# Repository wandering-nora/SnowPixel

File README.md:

# SnowPixel
Yet another 8x8 neopixel matrix... But hear me out, this one is a little special ❄️ 

This is a small 20x20x1.3mm module that can be seamlessly tiled without any wiring by soldering them together with the castellated holes.  
The built in solder jumpers in the data pads let the user decide whether the module sends and receives the data straight accross or at a 90 degree angle making any configuration possible.

The modules are meant to be used standalone or as an smd component in and of itself.  
The leds used are XL-1010RGBC-WS2812B 1x1mm leds which are the smallest currently available.  
If you have a clean 5V supply the capacitors on the back are usually not needed.  
This project is meant mainly as a test to push the pcb fab's specs to the limit and try a couple 3D printing ideas to obtain a thin, seamless display.

## 3D print
The 3D printed case is what brings the SnowPixel to life giving it proper square pixels. There's a standalone version for generic use and an smd version for when the pcb is soldered directly on a bigger pcb.  

The STL folder contains a bunch of common configurations, but the models are fully modular and can be easily edited with the OpenSCAD files.  

I'm currently experimenting with two methods for diffusing the light.  

### PET
These models are meant to be printed with PET (not PETG) on a PET diffusion film substrate.
This can be done by modifying a little the G-code to add an offset equal to the thickness of the film.

### PLA
These models are much simpler to print, they can be printed with normal pla (or any other plastic really) and only need the first layer to be printed in white and the rest in black.

 > Not an amazing render, I will update it with proper photos soon

## Manufacturing update
Even if quite out of spec for JLCPCB's cheapest offering (not paying for castellated holes and definitely going over spec for both the copper and silkscreen layers) the boards all turned out mostly fine!  
They definitely needed some cleanup as the edges were filled with burs from the castellated holes and the LED silkscreen wasn't printed all the way around.  
The boards are otherwise perfectly functional and pretty simple to assemble by hand with an hotplate.

#### Todo for v1.2
- [ ] Modify data jumpers for easier operation. (Maybe cuttable traces?)
- [ ] Make leds silkscreen thicker.

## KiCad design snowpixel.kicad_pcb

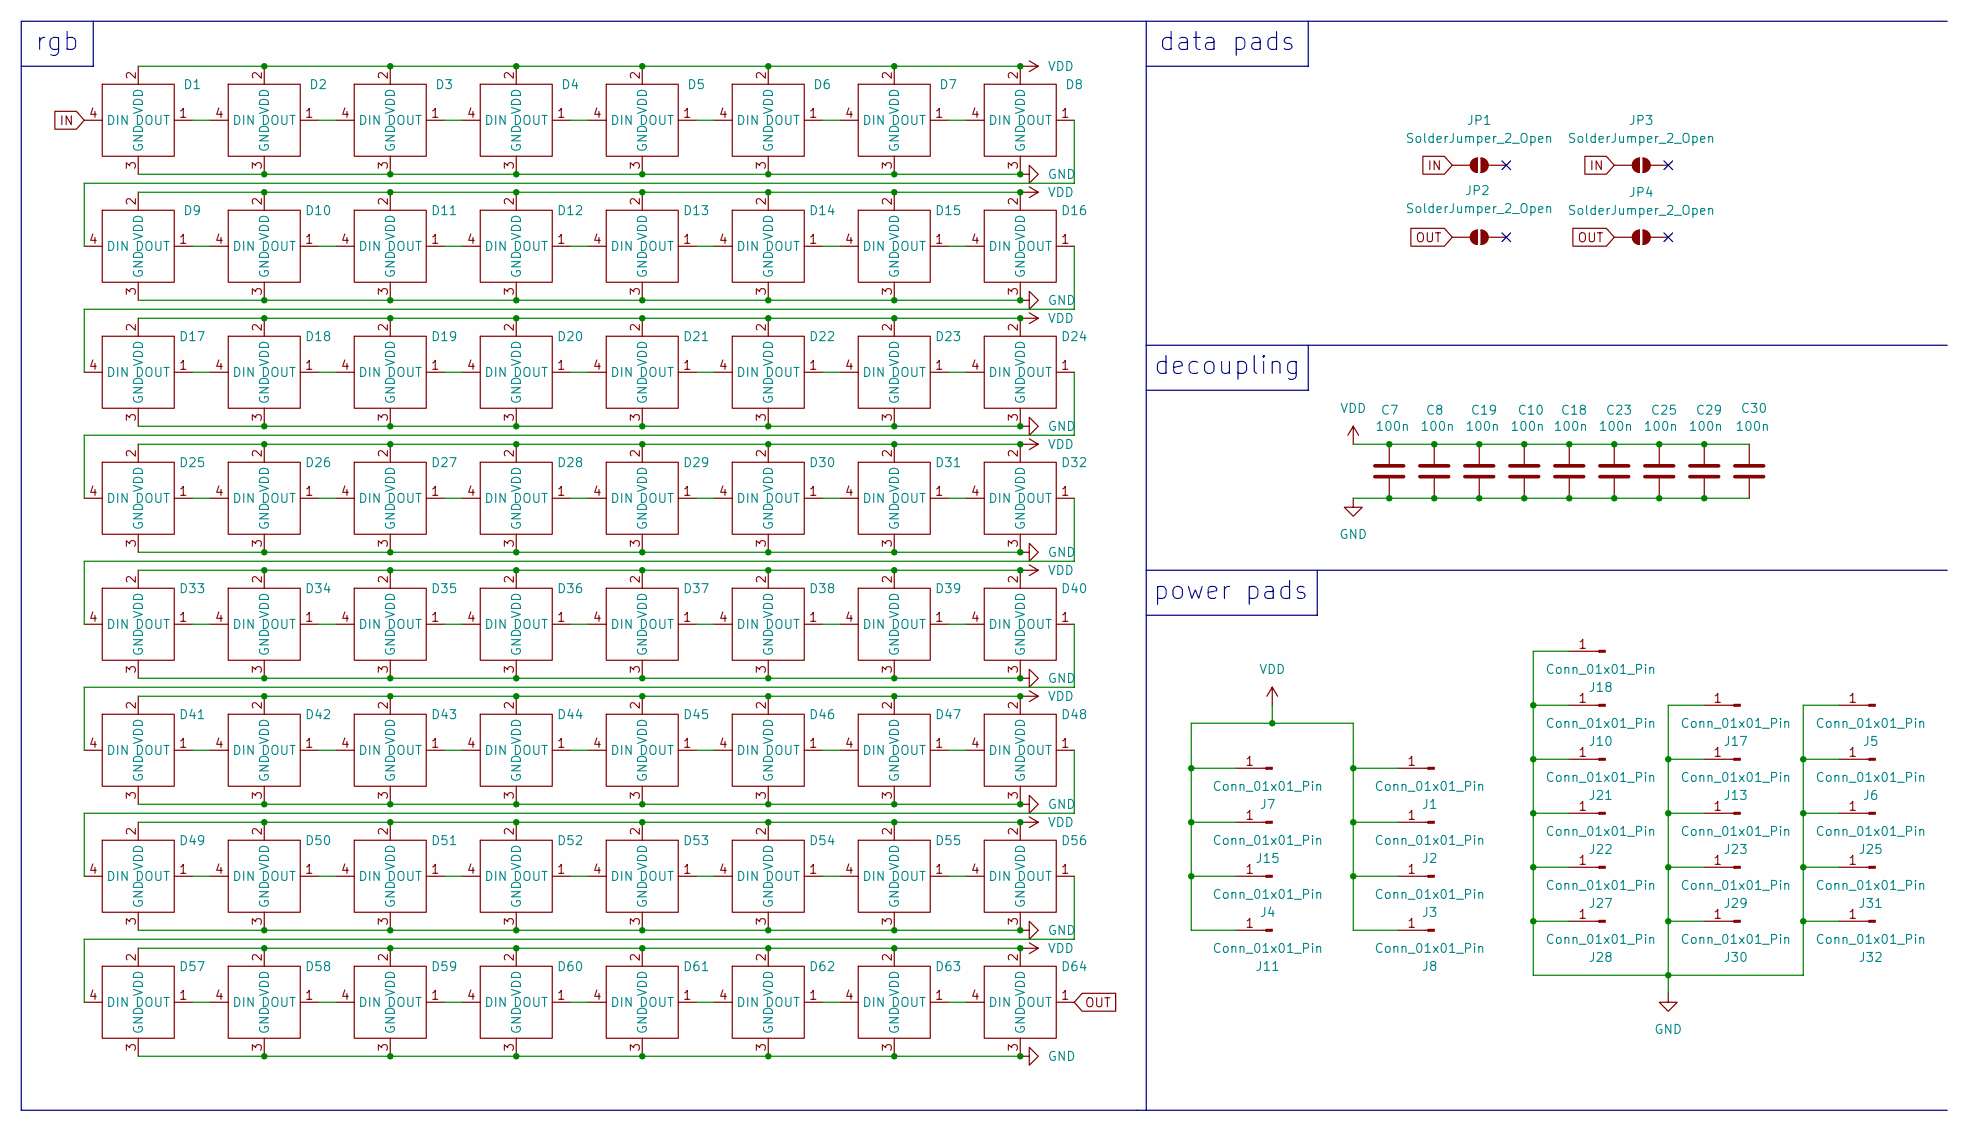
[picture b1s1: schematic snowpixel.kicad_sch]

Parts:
C7, C8, C10, C18, C19, C23, C25, C29, C30: 100n; C_0402_1005Metric
D1, D2, D3, D4, D5, D6, D7, D8, D9, D10, D11, D12, D13, D14, D15, D16, D17, D18, D19, D20, D21, D22, D23, D24, D25, D26, D27, D28, D29, D30, D31, D32, D33, D34, D35, D36, D37, D38, D39, D40, D41, D42, D43, D44, D45, D46, D47, D48, D49, D50, D51, D52, D53, D54, D55, D56, D57, D58, D59, D60, D61, D62, D63, D64: XL-1010RGBC-WS28128B
J1, J2, J3, J4, J7, J8, J11, J15: Conn_01x01_Pin; matrix-pad-vcc
J5, J6, J10, J13, J17, J18, J21, J22, J23, J25, J27, J28, J29, J30, J31, J32: Conn_01x01_Pin; matrix-pad-gn
JP1, JP3: SolderJumper_2_Open; matrix-pad-din
JP2, JP4: SolderJumper_2_Open; matrix-pad-dout

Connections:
GND: C7.2, C8.2, C10.2, C18.2, C19.2, C23.2, C25.2, C29.2, C30.2, D1.3 (GND), D2.3 (GND), D3.3 (GND), D4.3 (GND), D5.3 (GND), D6.3 (GND), D7.3 (GND), D8.3 (GND), D9.3 (GND), D10.3 (GND), D11.3 (GND), D12.3 (GND), D13.3 (GND), D14.3 (GND), D15.3 (GND), D16.3 (GND), D17.3 (GND), D18.3 (GND), D19.3 (GND), D20.3 (GND), D21.3 (GND), D22.3 (GND), D23.3 (GND), D24.3 (GND), D25.3 (GND), D26.3 (GND), D27.3 (GND), D28.3 (GND), D29.3 (GND), D30.3 (GND), D31.3 (GND), D32.3 (GND), D33.3 (GND), D34.3 (GND), D35.3 (GND), D36.3 (GND), D37.3 (GND), D38.3 (GND), D39.3 (GND), D40.3 (GND), D41.3 (GND), D42.3 (GND), D43.3 (GND), D44.3 (GND), D45.3 (GND), D46.3 (GND), D47.3 (GND), D48.3 (GND), D49.3 (GND), D50.3 (GND), D51.3 (GND), D52.3 (GND), D53.3 (GND), D54.3 (GND), D55.3 (GND), D56.3 (GND), D57.3 (GND), D58.3 (GND), D59.3 (GND), D60.3 (GND), D61.3 (GND), D62.3 (GND), D63.3 (GND), D64.3 (GND), J5.1, J6.1, J10.1, J13.1, J17.1, J18.1, J21.1, J22.1, J23.1, J25.1, J27.1, J28.1, J29.1, J30.1, J31.1, J32.1
IN: D1.4 (DIN), JP1.2 (B), JP3.2 (B)
unnamed: D1.1 (DOUT), D2.4 (DIN)
unnamed: D2.1 (DOUT), D3.4 (DIN)
unnamed: D3.1 (DOUT), D4.4 (DIN)
unnamed: D4.1 (DOUT), D5.4 (DIN)
unnamed: D5.1 (DOUT), D6.4 (DIN)
unnamed: D6.1 (DOUT), D7.4 (DIN)
unnamed: D7.1 (DOUT), D8.4 (DIN)
unnamed: D8.1 (DOUT), D9.4 (DIN)
unnamed: D9.1 (DOUT), D10.4 (DIN)
unnamed: D10.1 (DOUT), D11.4 (DIN)
unnamed: D11.1 (DOUT), D12.4 (DIN)
unnamed: D12.1 (DOUT), D13.4 (DIN)
unnamed: D13.1 (DOUT), D14.4 (DIN)
unnamed: D14.1 (DOUT), D15.4 (DIN)
unnamed: D15.1 (DOUT), D16.4 (DIN)
unnamed: D16.1 (DOUT), D17.4 (DIN)
unnamed: D17.1 (DOUT), D18.4 (DIN)
unnamed: D18.1 (DOUT), D19.4 (DIN)
unnamed: D19.1 (DOUT), D20.4 (DIN)
unnamed: D20.1 (DOUT), D21.4 (DIN)
unnamed: D21.1 (DOUT), D22.4 (DIN)
unnamed: D22.1 (DOUT), D23.4 (DIN)
unnamed: D23.1 (DOUT), D24.4 (DIN)
unnamed: D24.1 (DOUT), D25.4 (DIN)
unnamed: D25.1 (DOUT), D26.4 (DIN)
unnamed: D26.1 (DOUT), D27.4 (DIN)
unnamed: D27.1 (DOUT), D28.4 (DIN)
unnamed: D28.1 (DOUT), D29.4 (DIN)
unnamed: D29.1 (DOUT), D30.4 (DIN)
unnamed: D30.1 (DOUT), D31.4 (DIN)
unnamed: D31.1 (DOUT), D32.4 (DIN)
unnamed: D32.1 (DOUT), D33.4 (DIN)
unnamed: D33.1 (DOUT), D34.4 (DIN)
unnamed: D34.1 (DOUT), D35.4 (DIN)
unnamed: D35.1 (DOUT), D36.4 (DIN)
unnamed: D36.1 (DOUT), D37.4 (DIN)
unnamed: D37.1 (DOUT), D38.4 (DIN)
unnamed: D38.1 (DOUT), D39.4 (DIN)
unnamed: D39.1 (DOUT), D40.4 (DIN)
unnamed: D40.1 (DOUT), D41.4 (DIN)
unnamed: D41.1 (DOUT), D42.4 (DIN)
unnamed: D42.1 (DOUT), D43.4 (DIN)
unnamed: D43.1 (DOUT), D44.4 (DIN)
unnamed: D44.1 (DOUT), D45.4 (DIN)
unnamed: D45.1 (DOUT), D46.4 (DIN)
unnamed: D46.1 (DOUT), D47.4 (DIN)
unnamed: D47.1 (DOUT), D48.4 (DIN)
unnamed: D48.1 (DOUT), D49.4 (DIN)
unnamed: D49.1 (DOUT), D50.4 (DIN)
unnamed: D50.1 (DOUT), D51.4 (DIN)
unnamed: D51.1 (DOUT), D52.4 (DIN)
unnamed: D52.1 (DOUT), D53.4 (DIN)
unnamed: D53.1 (DOUT), D54.4 (DIN)
unnamed: D54.1 (DOUT), D55.4 (DIN)
unnamed: D55.1 (DOUT), D56.4 (DIN)
unnamed: D56.1 (DOUT), D57.4 (DIN)
unnamed: D57.1 (DOUT), D58.4 (DIN)
unnamed: D58.1 (DOUT), D59.4 (DIN)
unnamed: D59.1 (DOUT), D60.4 (DIN)
unnamed: D60.1 (DOUT), D61.4 (DIN)
unnamed: D61.1 (DOUT), D62.4 (DIN)
unnamed: D62.1 (DOUT), D63.4 (DIN)
unnamed: D63.1 (DOUT), D64.4 (DIN)
OUT: D64.1 (DOUT), JP2.2 (B), JP4.2 (B)
VDD: C7.1, C8.1, C10.1, C18.1, C19.1, C23.1, C25.1, C29.1, C30.1, D1.2 (VDD), D2.2 (VDD), D3.2 (VDD), D4.2 (VDD), D5.2 (VDD), D6.2 (VDD), D7.2 (VDD), D8.2 (VDD), D9.2 (VDD), D10.2 (VDD), D11.2 (VDD), D12.2 (VDD), D13.2 (VDD), D14.2 (VDD), D15.2 (VDD), D16.2 (VDD), D17.2 (VDD), D18.2 (VDD), D19.2 (VDD), D20.2 (VDD), D21.2 (VDD), D22.2 (VDD), D23.2 (VDD), D24.2 (VDD), D25.2 (VDD), D26.2 (VDD), D27.2 (VDD), D28.2 (VDD), D29.2 (VDD), D30.2 (VDD), D31.2 (VDD), D32.2 (VDD), D33.2 (VDD), D34.2 (VDD), D35.2 (VDD), D36.2 (VDD), D37.2 (VDD), D38.2 (VDD), D39.2 (VDD), D40.2 (VDD), D41.2 (VDD), D42.2 (VDD), D43.2 (VDD), D44.2 (VDD), D45.2 (VDD), D46.2 (VDD), D47.2 (VDD), D48.2 (VDD), D49.2 (VDD), D50.2 (VDD), D51.2 (VDD), D52.2 (VDD), D53.2 (VDD), D54.2 (VDD), D55.2 (VDD), D56.2 (VDD), D57.2 (VDD), D58.2 (VDD), D59.2 (VDD), D60.2 (VDD), D61.2 (VDD), D62.2 (VDD), D63.2 (VDD), D64.2 (VDD), J1.1, J2.1, J3.1, J4.1, J7.1, J8.1, J11.1, J15.1

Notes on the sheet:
data pads
power pads
rgb
decoupling

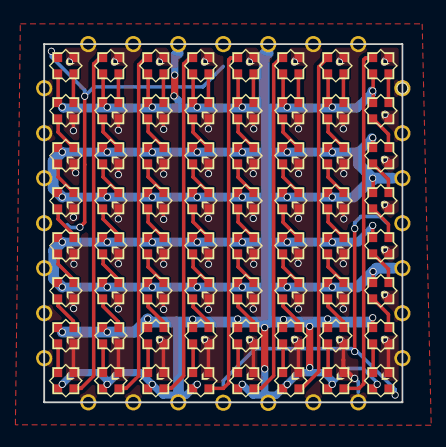
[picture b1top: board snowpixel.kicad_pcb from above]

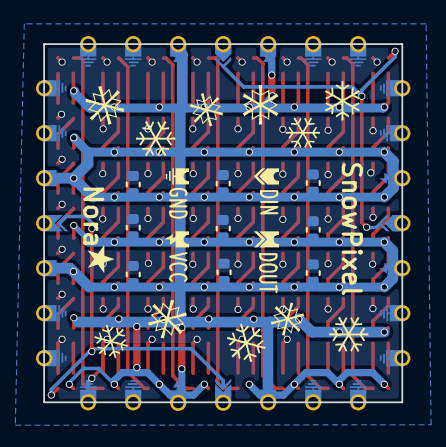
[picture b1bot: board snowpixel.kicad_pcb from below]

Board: 2 copper layers, 19.9 x 19.9 mm, 101 parts (37 on the bottom side), 67 nets.

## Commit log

2025-03-11 Initial commit with project files
2025-03-11 Add jlc preview images
2025-03-11 Fix silly image naming
2025-03-11 fix git mess
2025-03-11 Figure out readme flexbox
2025-03-11 Update image size in readme
2025-03-11 Update image padding in readme
2025-03-12 Change silkscreen text
2025-03-12 Update images
2025-03-15 Added v1 gerber files
2025-03-16 remove .gitignore
2025-03-18 Change folder structure for release
2025-03-20 Add fully modular OpenSCAD model
2025-03-20 Add 16x16 stl
2025-03-21 fix img alignment in readme
2025-03-23 Added 3d model for smd usage
2025-03-26 Added pla 3d models
2025-03-26 Removed stl files
2025-03-26 Renamed 3d models
2025-03-26 Add stl files and organize
2025-03-31 add blender render
2025-03-31 lower render res
2025-03-31 compress images more
2025-03-31 add 3d print images
2025-04-29 Removed unused images
2025-04-29 add license
